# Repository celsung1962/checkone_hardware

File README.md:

# CheckOne hardware

AQTech Power Prognostics · hardware of the CheckOne production test fixture: powers up to eight GapOne / FluxOne
sensors with 24 V, measures their 4–20 mA loops (3 × ADS1115, INA226), two NTC temperatures and the time (PCF8563),
with a 3.5" ESP32 display module and a web page; AK-P-08A DIN-rail enclosure. One board, **CheckOne**
(`hardware/CheckOne/`).

The repository was created on 2026-11-16 with the FluxOne_hardware / GapOne_V2 layout and repository policy
(kicad-schematic skill 1.6.0). It holds the v1 schematic and placement by S. Zimath, imported on 2026-11-16
(`reports/import_2026-11-16.md`), now revision 1.1 after the review (`reports/CheckOne/review_2026-11-16.md`), the
project documents and all later work.

```
checkone_hardware/
|-- CLAUDE.md                       design brief for Claude Code (v1 baseline, decisions, open items O1-O8)
|-- OUTSIDE_GIT.md                  what is kept outside git (OneDrive store CheckOne_Hardware) and how it gets there
|-- bitbucket-pipelines.yml         CI for Bitbucket: hardware checks, release build on <board>-v<version> tags, skill updates
|-- hw_checks.json                  config of tools/hw_checks (board CheckOne, checks, release prefix checkone)
|-- .claude/skills/                 kicad-schematic 1.6.0, kicad-placement 1.3.0, kicad-routing 1.29.0 (versioned with the project)
|-- docs/requirements/              CheckOne_requirements.md (consolidated), equipment description, web page, screen designs
|-- docs/datasheets/                PDFs + .txt + manifest.csv (fetch_datasheets.py), pin tables *_pins.csv
|-- reference/import_2026-11-16/    the hand-over (v1 zip, production files, large artifacts) - READ-ONLY, outside git (store)
|-- hardware/CheckOne/              KiCad 10 project, rev 1.1; hardware/*.py generate the schematic and sync the board
|-- calc/                           checkone_budget.py (measurement, NTC, fault current, power budget)
|-- bom/                            parts.csv (catalog data), jlc_summary.md, bom_summary.md
|-- DOC/                            deliverables (generated, outside git); DOC/source/ holds their sources
|-- reports/                        import report; reports/CheckOne/ for board work (Markdown in git)
`-- tools/                          hw_checks/ (checks, release), update_skills.py, filter_history.py (Bitbucket move)
```

## Tags

| Tag | Meaning |
|---|---|
| `<BOARD>_V<version>_fab_<date>` | the design as sent for fabrication (date of the production files) |
| `checkone-v<version>` | a board release: `tools/hw_checks/hw_release.py` builds and gates the package; the Bitbucket pipeline runs it on push |

## Checks

```
python tools/hw_checks/hw_checks.py                 ERC / DRC against tools/hw_checks/baseline, datasheet manifest
python tools/hw_checks/hw_release.py checkone-v1.1  release package and gate (build/release/<tag>/)
python calc/checkone_budget.py                      measurement, NTC, fault current and power budget of v1
python tools/update_skills.py                       newer skill releases (skills_hardware)
```

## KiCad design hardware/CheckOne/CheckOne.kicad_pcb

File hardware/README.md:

# hardware

The KiCad project of the CheckOne board (`CheckOne/`, KiCad 10) and the scripts that build it, as in GapOne V2.

| Script | Python | What it does |
|---|---|---|
| `build_symbol_lib.py` | any (sexpdata) | `CheckOne/CheckOne.kicad_sym`: project symbols from the KiCad 10 library or the pin table, fields, pins checked against `docs/datasheets/<part>_pins.csv`; log `symbol_build_log.md` |
| `check_all_symbols.py` | any | every project symbol against its pin table (skill `check_symbol_pins.py`) |
| `gen_checkone.py` | any | the schematic: root + 6 A4 sheets (`schgen.py`); never hand-edit the `.kicad_sch` |
| `sync_board.py` | KiCad | "Update PCB from Schematic": reloads every footprint from its library at the same place, sets values, fields, paths, nets; the rev 1.1 moves only once (board still at rev 1.0) |
| `schgen.py` | any | the schematic writer (GapOne copy, rev 1.1) |

After a schematic change:

```
python hardware/build_symbol_lib.py
python hardware/check_all_symbols.py
python hardware/gen_checkone.py
kicad-cli sch erc hardware/CheckOne/CheckOne.kicad_sch
kicad-cli sch export netlist --format kicadsexpr -o hardware/CheckOne/CheckOne.net hardware/CheckOne/CheckOne.kicad_sch
"C:\Program Files\KiCad\10.0\bin\python.exe" hardware/sync_board.py
python .claude/skills/kicad-schematic/scripts/check_drawing.py hardware/CheckOne/CheckOne.kicad_sch
python .claude/skills/kicad-schematic/scripts/fix_passive_text.py hardware/CheckOne
python tools/hw_checks/hw_checks.py
```

The v1 project of S. Zimath (KiCad 7, generated by his `gerador/design.py`) is in `reference/import_2026-11-16/`
(outside git) and in the git history up to commit `eac4dd2`.

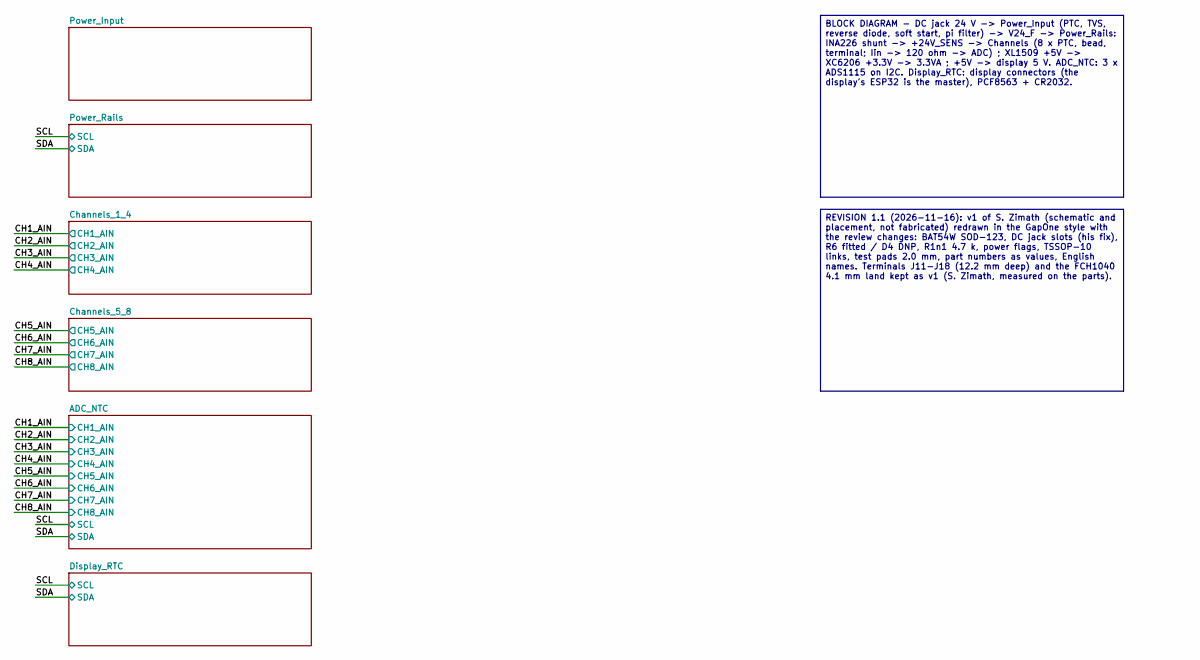
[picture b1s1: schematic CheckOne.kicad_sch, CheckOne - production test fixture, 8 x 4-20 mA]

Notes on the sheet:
BLOCK DIAGRAM - DC jack 24 V -> Power_Input (PTC, TVS, reverse diode, soft start, pi filter) -> V24_F -> Power_Rails: INA226 shunt -> +24V_SENS -> Channels (8 x PTC, bead, terminal; Iin -> 120 ohm -> ADC) ; XL1509 +5V -> XC6206 +3.3V -> 3.3VA ; +5V -> display 5 V. ADC_NTC: 3 x ADS1115 on I2C. Displ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
REVISION 1.1 (2026-11-16): v1 of S. Zimath (schematic and placement, not fabricated) redrawn in the GapOne style with the review changes: BAT54W SOD-123, DC jack slots (his fix), R6 fitted / D4 DNP, R1n1 4.7 k, power flags, TSSOP-10 links, test pads 2.0 mm, part numbers as values, English names. Te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

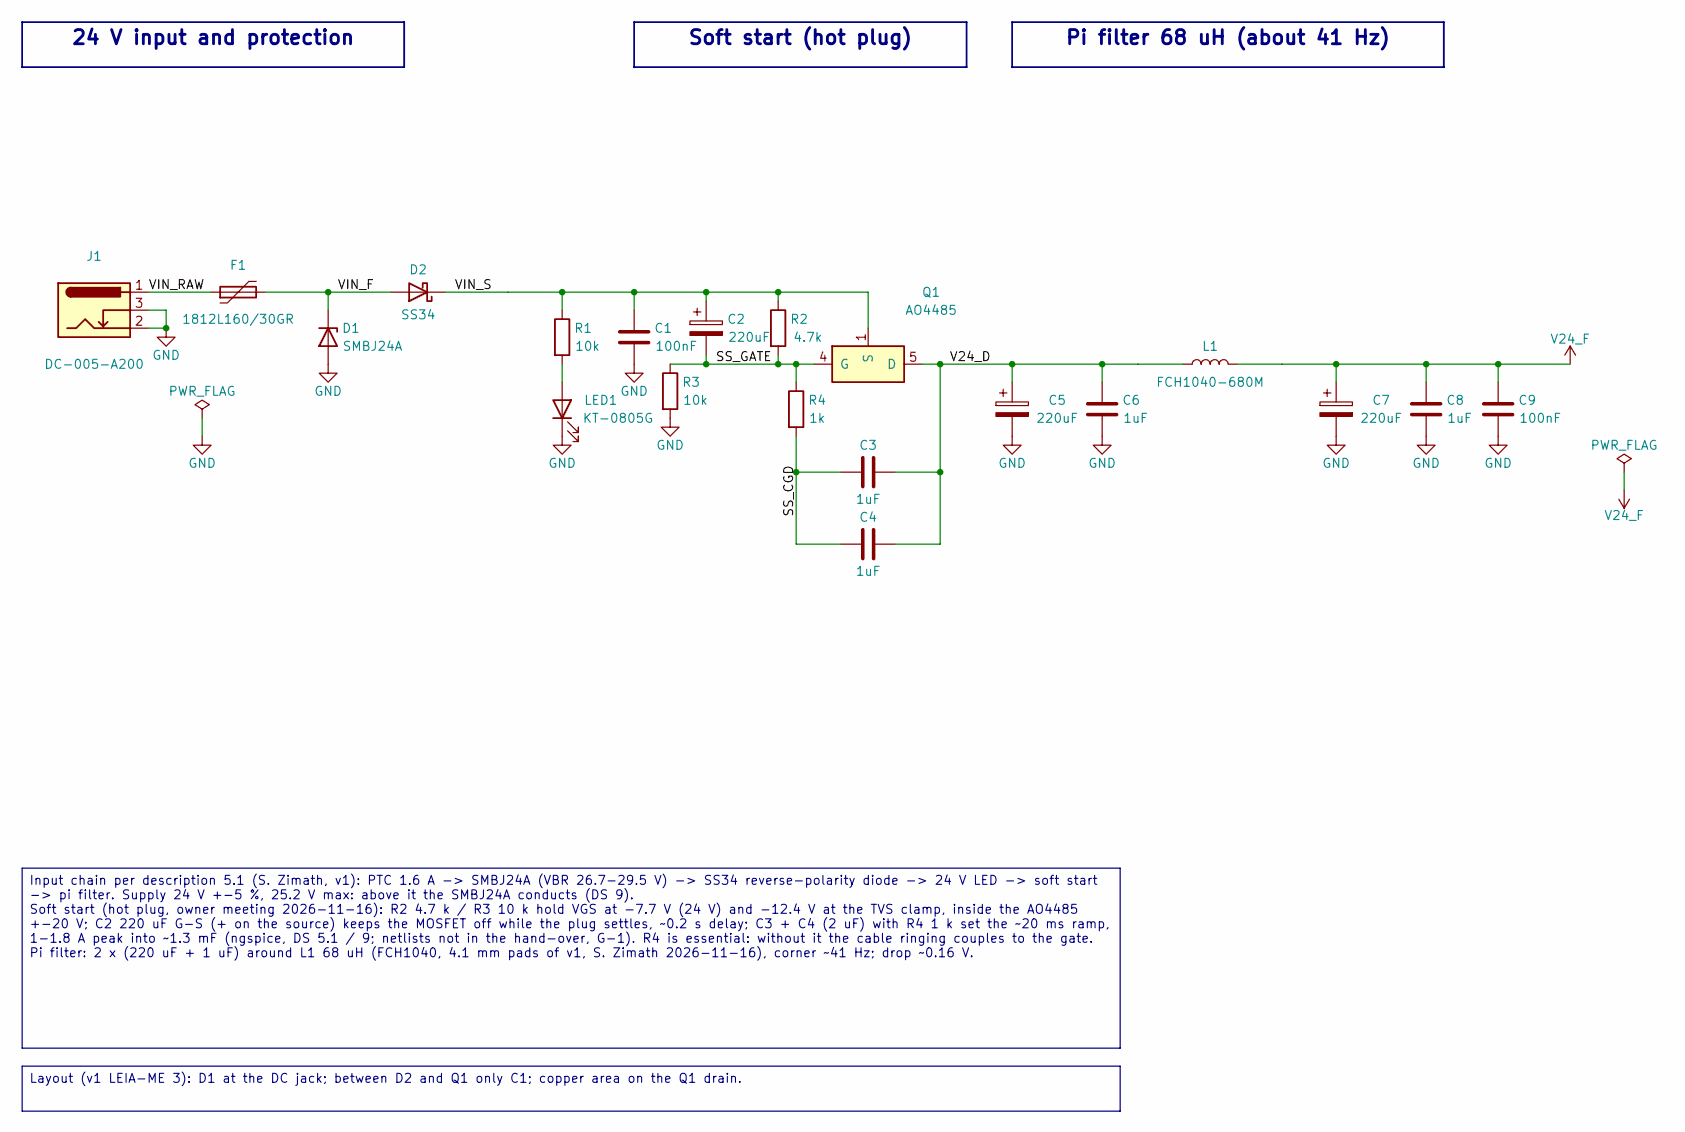
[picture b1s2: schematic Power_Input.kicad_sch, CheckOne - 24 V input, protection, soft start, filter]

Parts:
C1, C9: 100nF; C_0603_1608Metric; LCSC C14663
C2, C5, C7: 220uF; CP_Elec_10x10.5; LCSC C46550417
C3, C4, C6, C8: 1uF; C_0805_2012Metric; LCSC C28323
D1: SMBJ24A; D_SMB; LCSC C19077578
D2: SS34; D_SMA; LCSC C8678
F1: 1812L160/30GR; Fuse_1812_4532Metric; LCSC C18198337
J1: DC-005-A200; LCSC C720557
L1: FCH1040-680M; L_Fangcheng_FCH1040; LCSC C20415548
LED1: KT-0805G; LED_0805_2012Metric; LCSC C2297
Q1: AO4485; SOIC-8_3.9x4.9mm_P1.27mm; LCSC C5334068
R1, R3: 10k; R_0603_1608Metric; LCSC C25804
R2: 4.7k; R_0603_1608Metric; LCSC C23162
R4: 1k; R_0603_1608Metric; LCSC C21190

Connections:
/Power_Input/SS_CGD: C3.1, C4.1, R4.2
/Power_Input/SS_GATE: C2.2, Q1.4 (G), R2.2, R3.1, R4.1
/Power_Input/V24_D: C3.2, C4.2, C5.1, C6.1, L1.1, Q1.5 (D), Q1.6 (D), Q1.7 (D), Q1.8 (D)
/Power_Input/VIN_F: D1.1 (K), D2.2 (A), F1.2
/Power_Input/VIN_RAW: F1.1, J1.1
/Power_Input/VIN_S: C1.1, C2.1, D2.1 (K), Q1.1 (S), Q1.2 (S), Q1.3 (S), R1.1, R2.1
GND: C1.2, C5.2, C6.2, C7.2, C8.2, C9.2, D1.2 (A), J1.2, J1.3, LED1.1 (K), R3.2; also elsewhere on the board
unnamed: LED1.2 (A), R1.2
V24_F: C7.1, C8.1, C9.1, L1.2; also elsewhere on the board

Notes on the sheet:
24 V input and protection
Soft start (hot plug)
Pi filter 68 uH (about 41 Hz)
Input chain per description 5.1 (S. Zimath, v1): PTC 1.6 A -> SMBJ24A (VBR 26.7-29.5 V) -> SS34 reverse-polarity diode -> 24 V LED -> soft start -> pi filter. Supply 24 V +-5 %, 25.2 V max: above it the SMBJ24A conducts (DS 9). Soft start (hot plug, owner meeting 2026-11-16): R2 4.7 k / R3 10 k hol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
Layout (v1 LEIA-ME 3): D1 at the DC jack; between D2 and Q1 only C1; copper area on the Q1 drain.

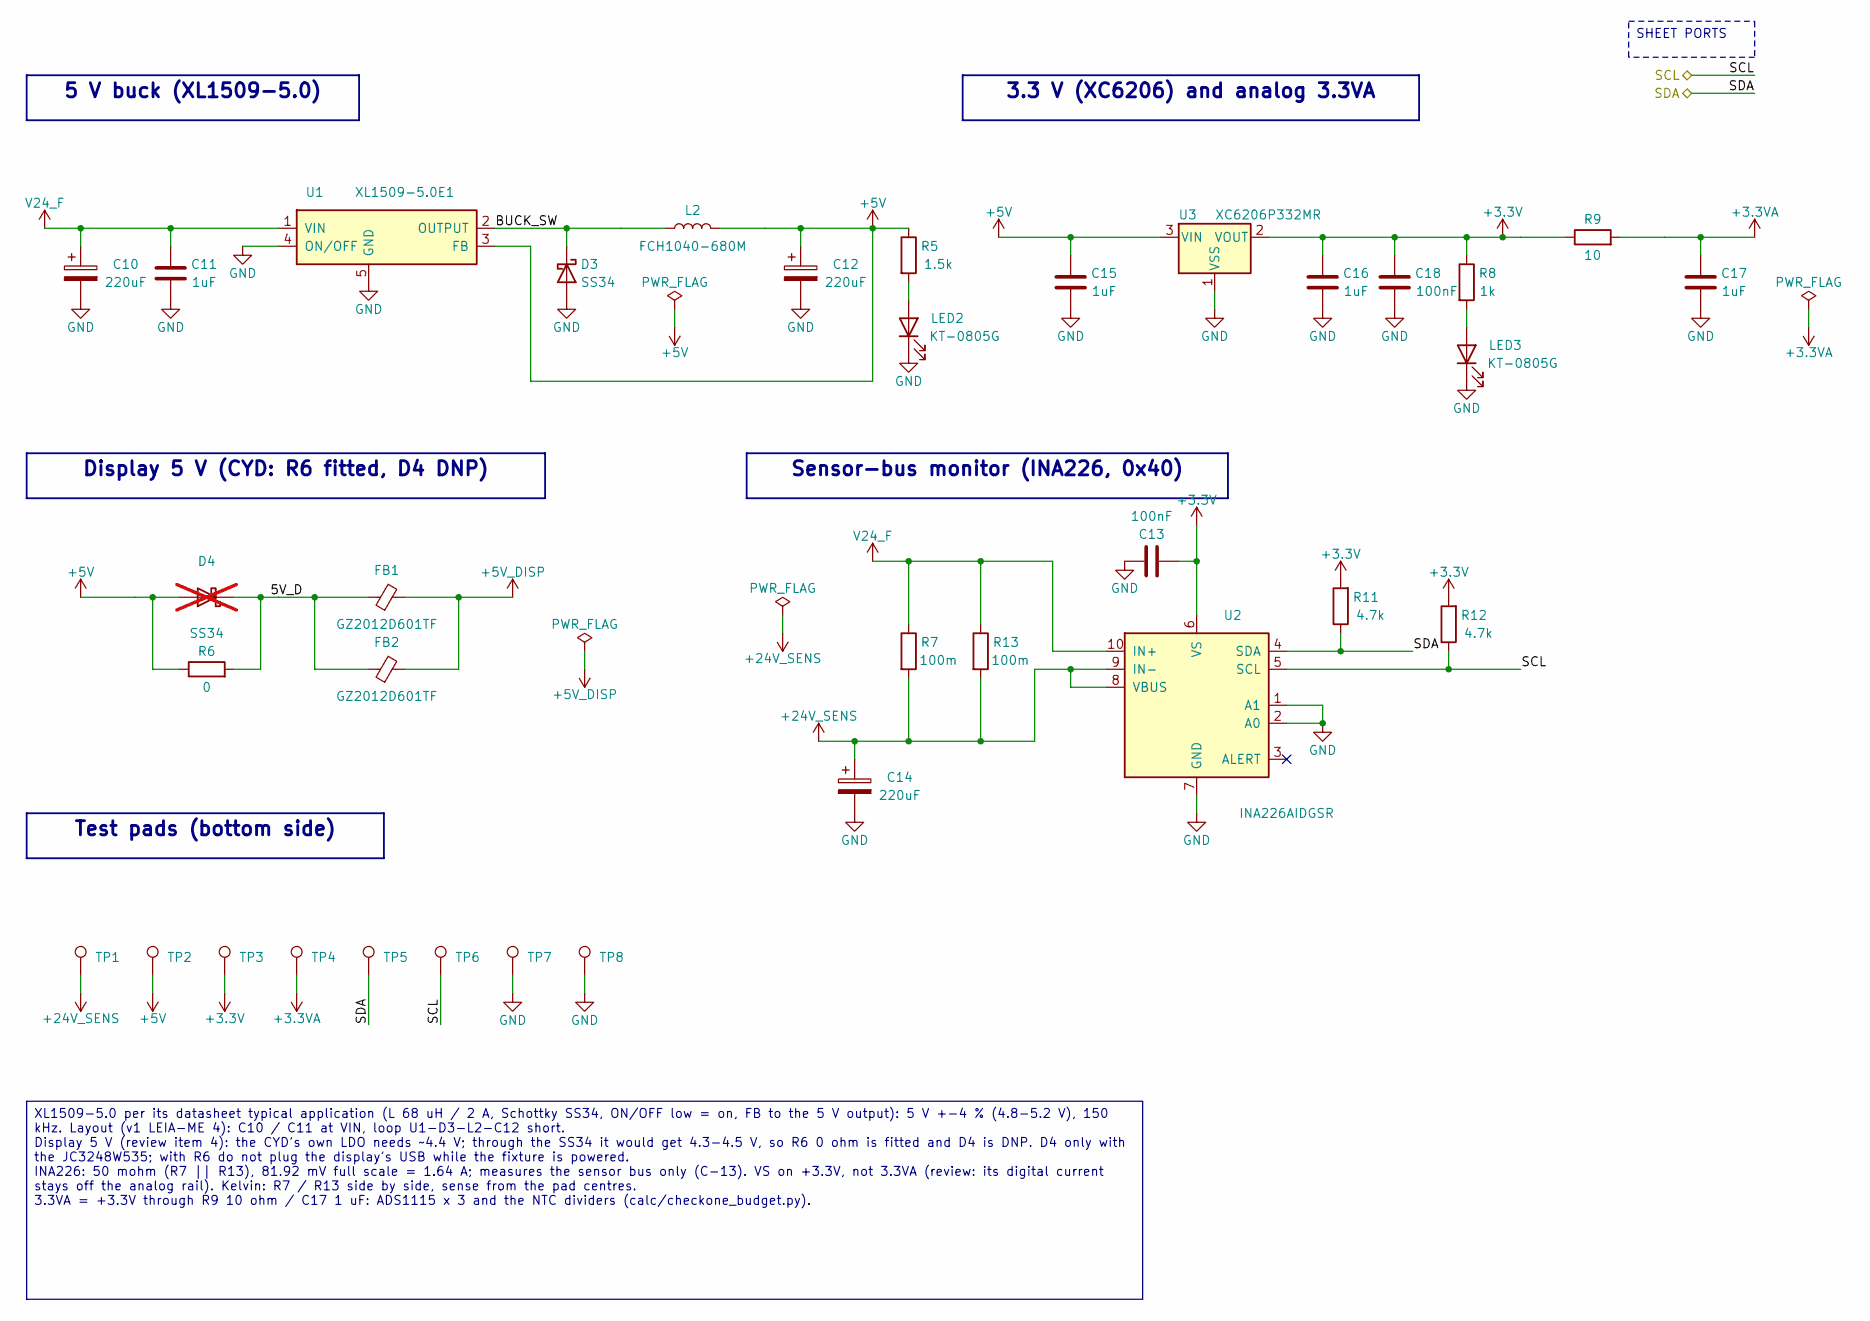
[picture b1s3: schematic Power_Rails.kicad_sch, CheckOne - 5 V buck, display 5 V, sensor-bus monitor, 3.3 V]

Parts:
C10, C12, C14: 220uF; CP_Elec_10x10.5; LCSC C46550417
C11, C15, C16, C17: 1uF; C_0805_2012Metric; LCSC C28323
C13, C18: 100nF; C_0603_1608Metric; LCSC C14663
D3: SS34; D_SMA; LCSC C8678
D4: SS34; D_SMA; LCSC C8678; not fitted
FB1, FB2: GZ2012D601TF; L_0805_2012Metric; LCSC C1017
L2: FCH1040-680M; L_Fangcheng_FCH1040; LCSC C20415548
LED2, LED3: KT-0805G; LED_0805_2012Metric; LCSC C2297
R5: 1.5k; R_0603_1608Metric; LCSC C22843
R6: 0; R_0603_1608Metric; LCSC C21189
R7, R13: 100m; R_1206_3216Metric; LCSC C25334
R8: 1k; R_0603_1608Metric; LCSC C21190
R9: 10; R_0603_1608Metric; LCSC C22859
R11, R12: 4.7k; R_0603_1608Metric; LCSC C23162
TP1, TP2, TP3, TP4, TP5, TP6, TP7, TP8: TP; TestPoint_Pad_D2.0mm
U1: XL1509-5.0E1; SOIC-8_3.9x4.9mm_P1.27mm; LCSC C61063
U2: INA226AIDGSR; TSSOP-10_3x3mm_P0.5mm; LCSC C49851
U3: XC6206P332MR; SOT-23; LCSC C5446

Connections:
+3.3V: C13.1, C16.1, C18.1, R8.1, R9.1, R11.2, R12.2, TP3.1 (1_1), U2.6 (VS), U3.2 (VOUT); also elsewhere on the board
+3.3VA: C17.1, R9.2, TP4.1 (1_1); also elsewhere on the board
+5V: C12.1, C15.1, D4.2 (A), L2.2, R5.1, R6.1, TP2.1 (1_1), U1.3 (FB), U3.3 (VIN)
+5V_DISP: FB1.2, FB2.2; also elsewhere on the board
+24V_SENS: C14.1, R7.2, R13.2, TP1.1 (1_1), U2.8 (VBUS), U2.9 (IN-); also elsewhere on the board
/Power_Rails/5V_D: D4.1 (K), FB1.1, FB2.1, R6.2
/Power_Rails/BUCK_SW: D3.1 (K), L2.1, U1.2 (OUTPUT)
/SCL: R12.1, TP6.1 (1_1), U2.5 (SCL); also elsewhere on the board
/SDA: R11.1, TP5.1 (1_1), U2.4 (SDA); also elsewhere on the board
GND: C10.2, C11.2, C12.2, C13.2, C14.2, C15.2, C16.2, C17.2, C18.2, D3.2 (A), LED2.1 (K), LED3.1 (K), TP7.1 (1_1), TP8.1 (1_1), U1.4 (ON/OFF), U1.5 (GND), U1.6 (GND), U1.7 (GND), U1.8 (GND), U2.1 (A1), U2.2 (A0), U2.7 (GND), U3.1 (VSS); also elsewhere on the board
unnamed: LED2.2 (A), R5.2
unnamed: LED3.2 (A), R8.2
V24_F: C10.1, C11.1, R7.1, R13.1, U1.1 (VIN), U2.10 (IN+); also elsewhere on the board

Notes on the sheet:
5 V buck (XL1509-5.0)
3.3 V (XC6206) and analog 3.3VA
Display 5 V (CYD: R6 fitted, D4 DNP)
Sensor-bus monitor (INA226, 0x40)
Test pads (bottom side)
XL1509-5.0 per its datasheet typical application (L 68 uH / 2 A, Schottky SS34, ON/OFF low = on, FB to the 5 V output): 5 V +-4 % (4.8-5.2 V), 150 kHz. Layout (v1 LEIA-ME 4): C10 / C11 at VIN, loop U1-D3-L2-C12 short. Display 5 V (review item 4): the CYD's own LDO needs ~4.4 V; through the SS34 it 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
SHEET PORTS

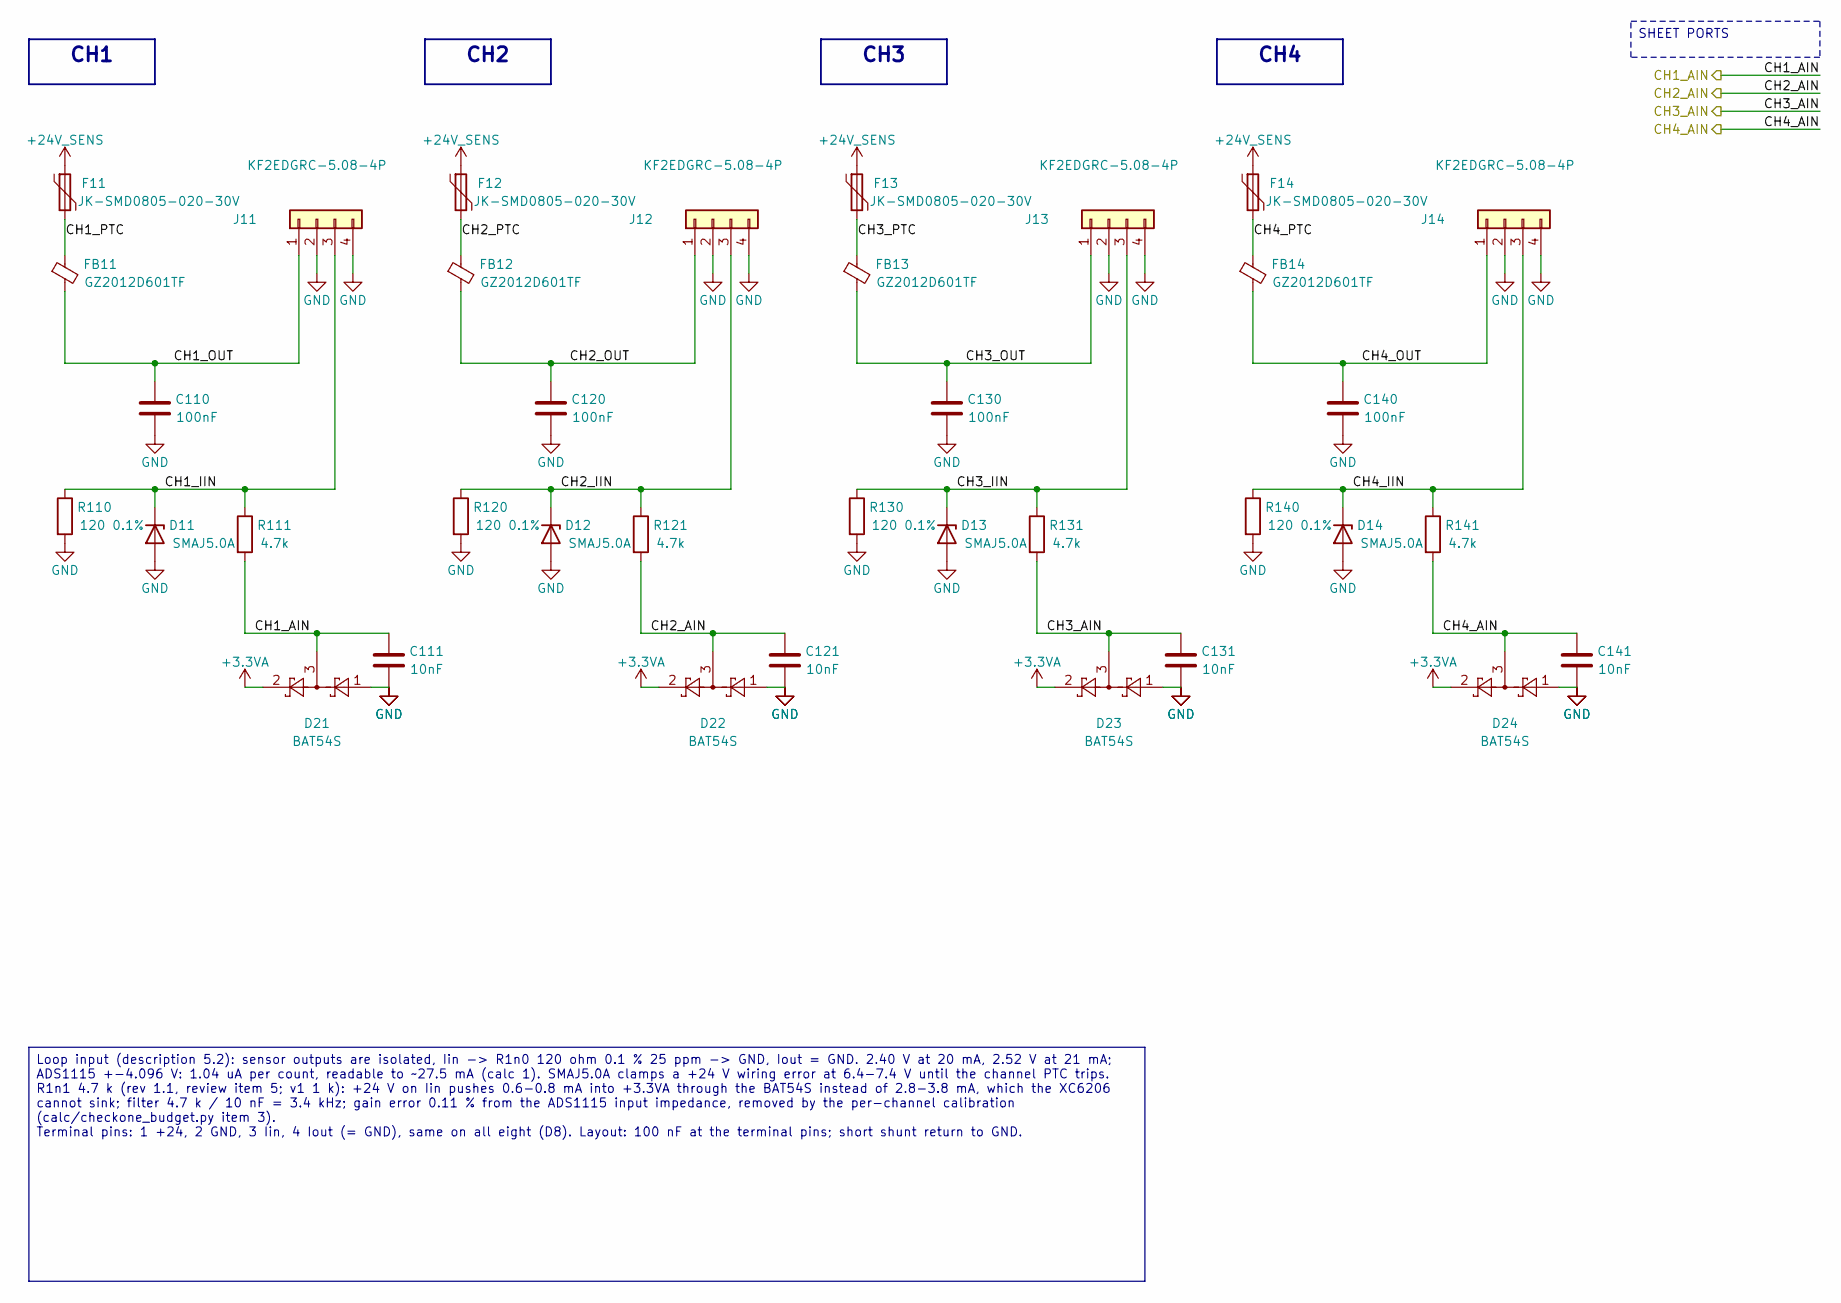
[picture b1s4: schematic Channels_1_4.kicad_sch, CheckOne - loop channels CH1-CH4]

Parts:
C110, C120, C130, C140: 100nF; C_0603_1608Metric; LCSC C14663
C111, C121, C131, C141: 10nF; C_0603_1608Metric; LCSC C57112
D11, D12, D13, D14: SMAJ5.0A; D_SMA; LCSC C2925443
D21, D22, D23, D24: BAT54S; SOT-23; LCSC C7420333
F11, F12, F13, F14: JK-SMD0805-020-30V; Fuse_0805_2012Metric; LCSC C516070
FB11, FB12, FB13, FB14: GZ2012D601TF; L_0805_2012Metric; LCSC C1017
J11, J12, J13, J14: KF2EDGRC-5.08-4P; LCSC C441238
R110, R120, R130, R140: 120 0.1%; R_1206_3216Metric; LCSC C2989146
R111, R121, R131, R141: 4.7k; R_0603_1608Metric; LCSC C23162

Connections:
+3.3VA: D21.2 (K2), D22.2 (K2), D23.2 (K2), D24.2 (K2); also elsewhere on the board
+24V_SENS: F11.1, F12.1, F13.1, F14.1; also elsewhere on the board
/CH1_AIN: C111.1, D21.3 (K1/A2), R111.2; also elsewhere on the board
/CH2_AIN: C121.1, D22.3 (K1/A2), R121.2; also elsewhere on the board
/CH3_AIN: C131.1, D23.3 (K1/A2), R131.2; also elsewhere on the board
/CH4_AIN: C141.1, D24.3 (K1/A2), R141.2; also elsewhere on the board
/Channels_1_4/CH1_IIN: D11.1 (K), J11.3, R110.1, R111.1
/Channels_1_4/CH1_OUT: C110.1, FB11.2, J11.1
/Channels_1_4/CH1_PTC: F11.2, FB11.1
/Channels_1_4/CH2_IIN: D12.1 (K), J12.3, R120.1, R121.1
/Channels_1_4/CH2_OUT: C120.1, FB12.2, J12.1
/Channels_1_4/CH2_PTC: F12.2, FB12.1
/Channels_1_4/CH3_IIN: D13.1 (K), J13.3, R130.1, R131.1
/Channels_1_4/CH3_OUT: C130.1, FB13.2, J13.1
/Channels_1_4/CH3_PTC: F13.2, FB13.1
/Channels_1_4/CH4_IIN: D14.1 (K), J14.3, R140.1, R141.1
/Channels_1_4/CH4_OUT: C140.1, FB14.2, J14.1
/Channels_1_4/CH4_PTC: F14.2, FB14.1
GND: C110.2, C111.2, C120.2, C121.2, C130.2, C131.2, C140.2, C141.2, D11.2 (A), D12.2 (A), D13.2 (A), D14.2 (A), D21.1 (A1), D22.1 (A1), D23.1 (A1), D24.1 (A1), J11.2, J11.4, J12.2, J12.4, J13.2, J13.4, J14.2, J14.4, R110.2, R120.2, R130.2, R140.2; also elsewhere on the board

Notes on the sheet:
CH1
CH2
CH3
CH4
Loop input (description 5.2): sensor outputs are isolated, Iin -> R1n0 120 ohm 0.1 % 25 ppm -> GND, Iout = GND. 2.40 V at 20 mA, 2.52 V at 21 mA; ADS1115 +-4.096 V: 1.04 uA per count, readable to ~27.5 mA (calc 1). SMAJ5.0A clamps a +24 V wiring error at 6.4-7.4 V until the channel PTC trips. R1n1 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
SHEET PORTS

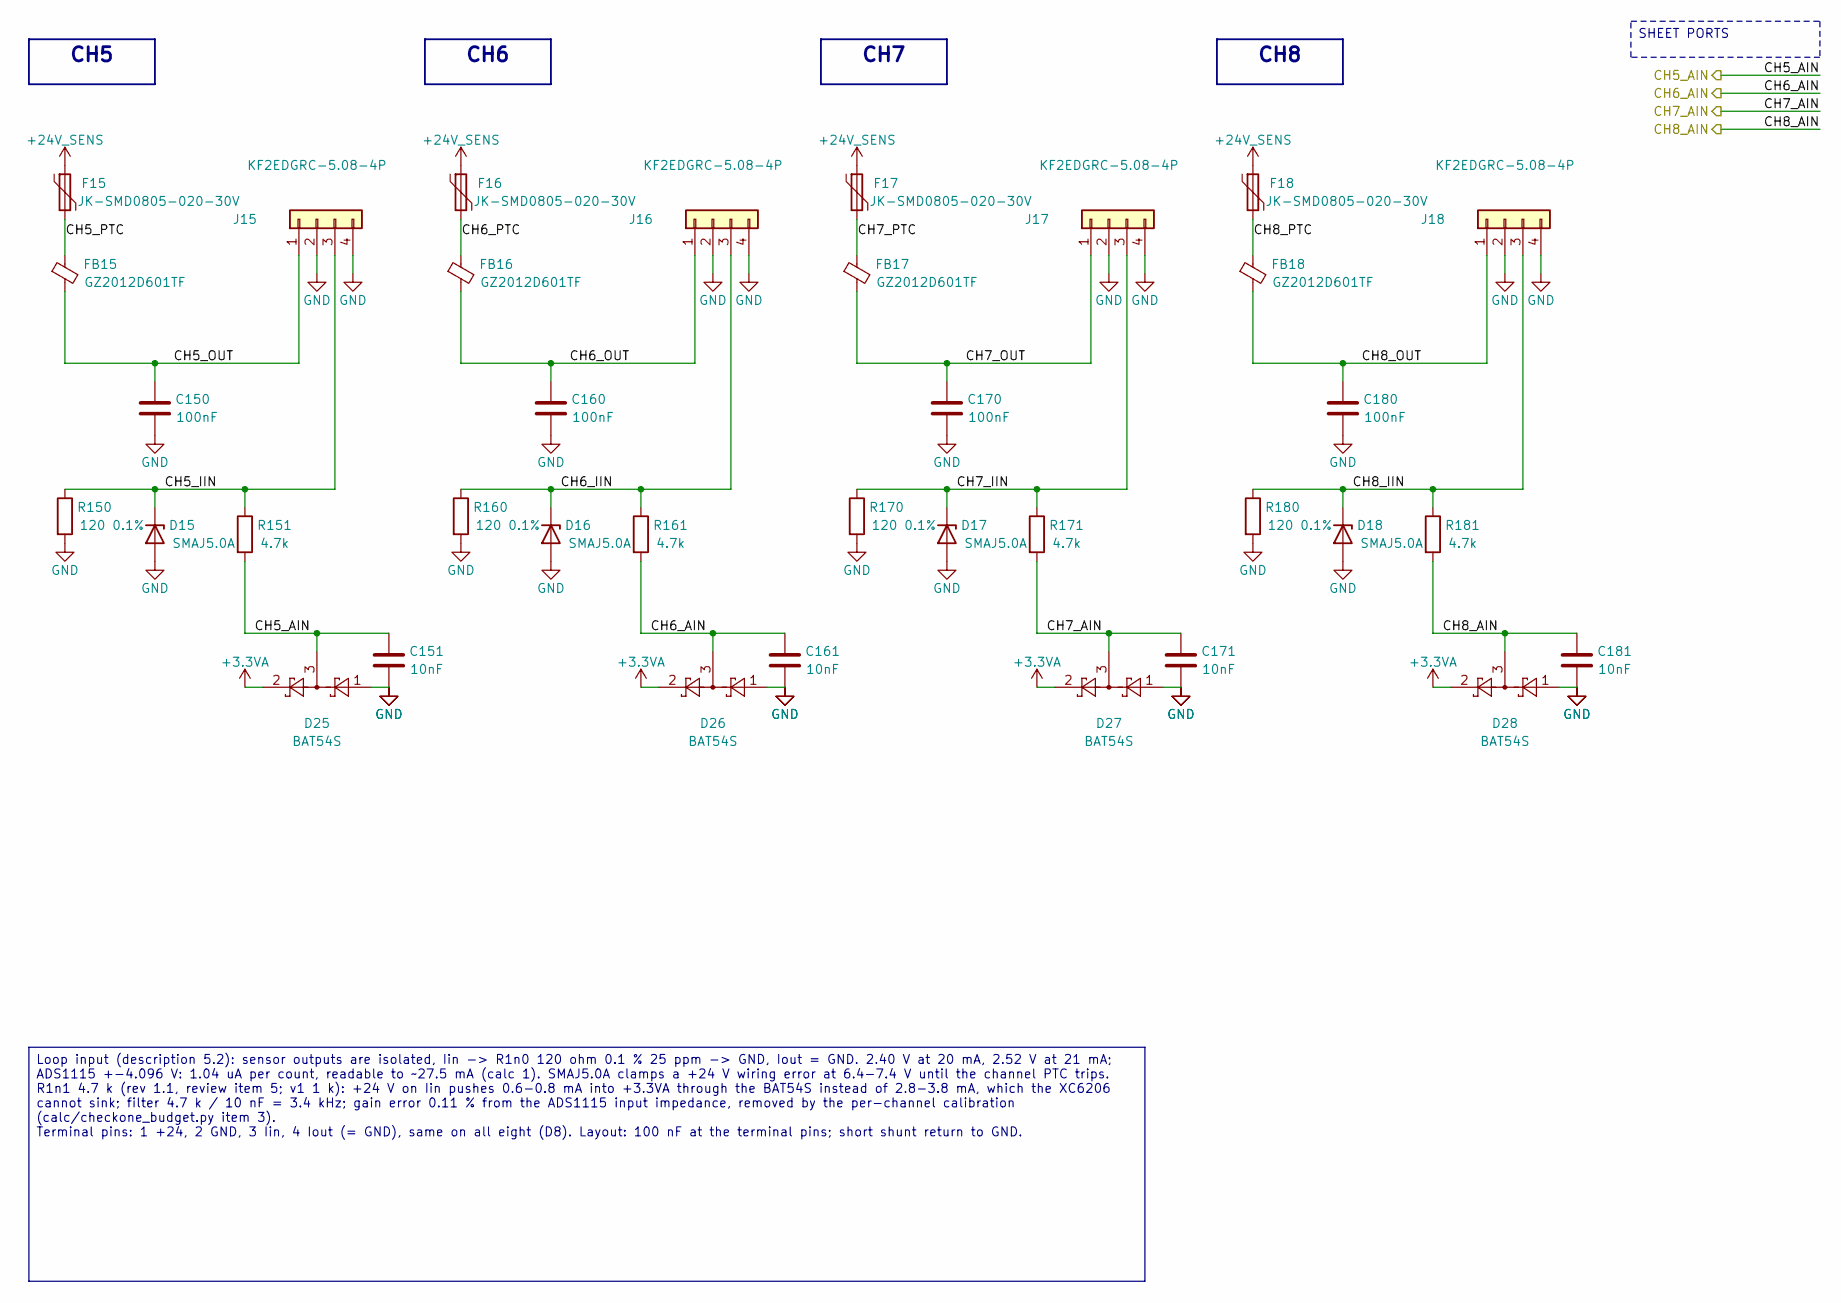
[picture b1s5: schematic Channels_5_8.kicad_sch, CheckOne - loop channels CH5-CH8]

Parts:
C150, C160, C170, C180: 100nF; C_0603_1608Metric; LCSC C14663
C151, C161, C171, C181: 10nF; C_0603_1608Metric; LCSC C57112
D15, D16, D17, D18: SMAJ5.0A; D_SMA; LCSC C2925443
D25, D26, D27, D28: BAT54S; SOT-23; LCSC C7420333
F15, F16, F17, F18: JK-SMD0805-020-30V; Fuse_0805_2012Metric; LCSC C516070
FB15, FB16, FB17, FB18: GZ2012D601TF; L_0805_2012Metric; LCSC C1017
J15, J16, J17, J18: KF2EDGRC-5.08-4P; LCSC C441238
R150, R160, R170, R180: 120 0.1%; R_1206_3216Metric; LCSC C2989146
R151, R161, R171, R181: 4.7k; R_0603_1608Metric; LCSC C23162

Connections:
+3.3VA: D25.2 (K2), D26.2 (K2), D27.2 (K2), D28.2 (K2); also elsewhere on the board
+24V_SENS: F15.1, F16.1, F17.1, F18.1; also elsewhere on the board
/CH5_AIN: C151.1, D25.3 (K1/A2), R151.2; also elsewhere on the board
/CH6_AIN: C161.1, D26.3 (K1/A2), R161.2; also elsewhere on the board
/CH7_AIN: C171.1, D27.3 (K1/A2), R171.2; also elsewhere on the board
/CH8_AIN: C181.1, D28.3 (K1/A2), R181.2; also elsewhere on the board
/Channels_5_8/CH5_IIN: D15.1 (K), J15.3, R150.1, R151.1
/Channels_5_8/CH5_OUT: C150.1, FB15.2, J15.1
/Channels_5_8/CH5_PTC: F15.2, FB15.1
/Channels_5_8/CH6_IIN: D16.1 (K), J16.3, R160.1, R161.1
/Channels_5_8/CH6_OUT: C160.1, FB16.2, J16.1
/Channels_5_8/CH6_PTC: F16.2, FB16.1
/Channels_5_8/CH7_IIN: D17.1 (K), J17.3, R170.1, R171.1
/Channels_5_8/CH7_OUT: C170.1, FB17.2, J17.1
/Channels_5_8/CH7_PTC: F17.2, FB17.1
/Channels_5_8/CH8_IIN: D18.1 (K), J18.3, R180.1, R181.1
/Channels_5_8/CH8_OUT: C180.1, FB18.2, J18.1
/Channels_5_8/CH8_PTC: F18.2, FB18.1
GND: C150.2, C151.2, C160.2, C161.2, C170.2, C171.2, C180.2, C181.2, D15.2 (A), D16.2 (A), D17.2 (A), D18.2 (A), D25.1 (A1), D26.1 (A1), D27.1 (A1), D28.1 (A1), J15.2, J15.4, J16.2, J16.4, J17.2, J17.4, J18.2, J18.4, R150.2, R160.2, R170.2, R180.2; also elsewhere on the board

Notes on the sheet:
CH5
CH6
CH7
CH8
Loop input (description 5.2): sensor outputs are isolated, Iin -> R1n0 120 ohm 0.1 % 25 ppm -> GND, Iout = GND. 2.40 V at 20 mA, 2.52 V at 21 mA; ADS1115 +-4.096 V: 1.04 uA per count, readable to ~27.5 mA (calc 1). SMAJ5.0A clamps a +24 V wiring error at 6.4-7.4 V until the channel PTC trips. R1n1 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
SHEET PORTS

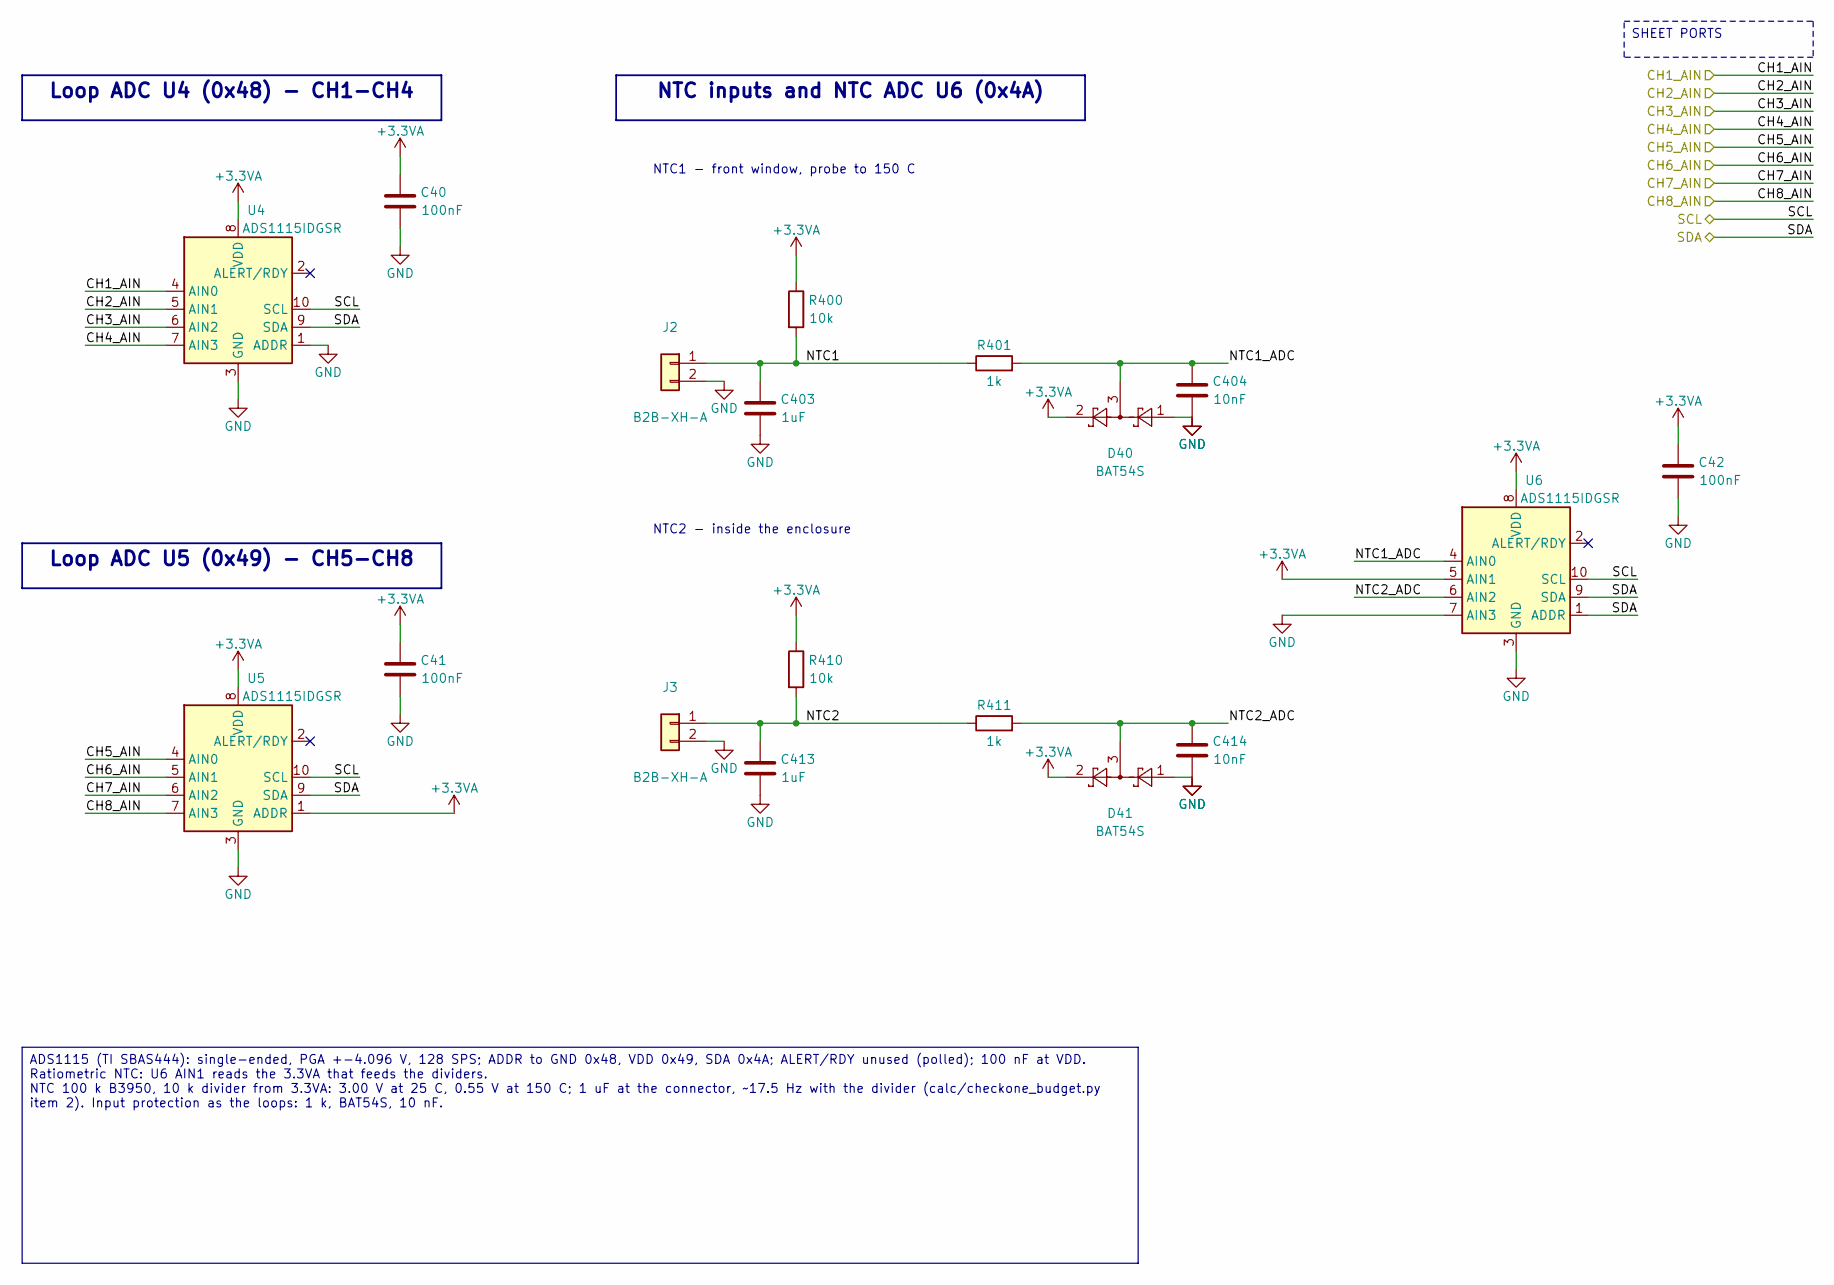
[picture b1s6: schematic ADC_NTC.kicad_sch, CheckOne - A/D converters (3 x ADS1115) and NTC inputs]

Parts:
C40, C41, C42: 100nF; C_0603_1608Metric; LCSC C14663
C403, C413: 1uF; C_0805_2012Metric; LCSC C28323
C404, C414: 10nF; C_0603_1608Metric; LCSC C57112
D40, D41: BAT54S; SOT-23; LCSC C7420333
J2, J3: B2B-XH-A; JST_XH_B2B-XH-A_1x02_P2.50mm_Vertical; LCSC C158012
R400, R410: 10k; R_0603_1608Metric; LCSC C25804
R401, R411: 1k; R_0603_1608Metric; LCSC C21190
U4, U5, U6: ADS1115IDGSR; TSSOP-10_3x3mm_P0.5mm; LCSC C37593

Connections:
+3.3VA: C40.1, C41.1, C42.1, D40.2 (K2), D41.2 (K2), R400.1, R410.1, U4.8 (VDD), U5.1 (ADDR), U5.8 (VDD), U6.5 (AIN1), U6.8 (VDD); also elsewhere on the board
/ADC_NTC/NTC1: C403.1, J2.1, R400.2, R401.1
/ADC_NTC/NTC1_ADC: C404.1, D40.3 (K1/A2), R401.2, U6.4 (AIN0)
/ADC_NTC/NTC2: C413.1, J3.1, R410.2, R411.1
/ADC_NTC/NTC2_ADC: C414.1, D41.3 (K1/A2), R411.2, U6.6 (AIN2)
/CH1_AIN: U4.4 (AIN0); also elsewhere on the board
/CH2_AIN: U4.5 (AIN1); also elsewhere on the board
/CH3_AIN: U4.6 (AIN2); also elsewhere on the board
/CH4_AIN: U4.7 (AIN3); also elsewhere on the board
/CH5_AIN: U5.4 (AIN0); also elsewhere on the board
/CH6_AIN: U5.5 (AIN1); also elsewhere on the board
/CH7_AIN: U5.6 (AIN2); also elsewhere on the board
/CH8_AIN: U5.7 (AIN3); also elsewhere on the board
/SCL: U4.10 (SCL), U5.10 (SCL), U6.10 (SCL); also elsewhere on the board
/SDA: U4.9 (SDA), U5.9 (SDA), U6.1 (ADDR), U6.9 (SDA); also elsewhere on the board
GND: C40.2, C41.2, C42.2, C403.2, C404.2, C413.2, C414.2, D40.1 (A1), D41.1 (A1), J2.2, J3.2, U4.1 (ADDR), U4.3 (GND), U5.3 (GND), U6.3 (GND), U6.7 (AIN3); also elsewhere on the board

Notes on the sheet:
Loop ADC U4 (0x48) - CH1-CH4
Loop ADC U5 (0x49) - CH5-CH8
NTC inputs and NTC ADC U6 (0x4A)
NTC1 - front window, probe to 150 C
NTC2 - inside the enclosure
ADS1115 (TI SBAS444): single-ended, PGA +-4.096 V, 128 SPS; ADDR to GND 0x48, VDD 0x49, SDA 0x4A; ALERT/RDY unused (polled); 100 nF at VDD. Ratiometric NTC: U6 AIN1 reads the 3.3VA that feeds the dividers. NTC 100 k B3950, 10 k divider from 3.3VA: 3.00 V at 25 C, 0.55 V at 150 C; 1 uF at the connec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
SHEET PORTS

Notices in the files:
hardware/gen_checkone.py:
notes that cite the datasheet figure and the calc/ script of every value. The generator is the master copy of
